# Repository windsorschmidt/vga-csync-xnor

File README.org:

* About

Combines VGA horizontal and vertical synchronization signals into 75Ω
composite sync for use with analog CRT displays such as PVMs/BVM's, or
televisions with RGBS inputs, e.g. SCART or RGB-modified televisions.

[[vga-csync-xnor.png?raw=true]]

* EDID EEPROM

An on-board EEPROM allows the adapter to store and serve an EDID to
the host PC to automatically configure a TV-compatible video mode.

In Linux, [[https://github.com/ChalkElec/write-edid][write-edid]] may be used to program the EEPROM with an
EDID. Sample EDID files have been included.

* License

Circuit schematic and PCB layout are licensed under CERN-OHL-S v2.

See [[LICENSE.txt]].

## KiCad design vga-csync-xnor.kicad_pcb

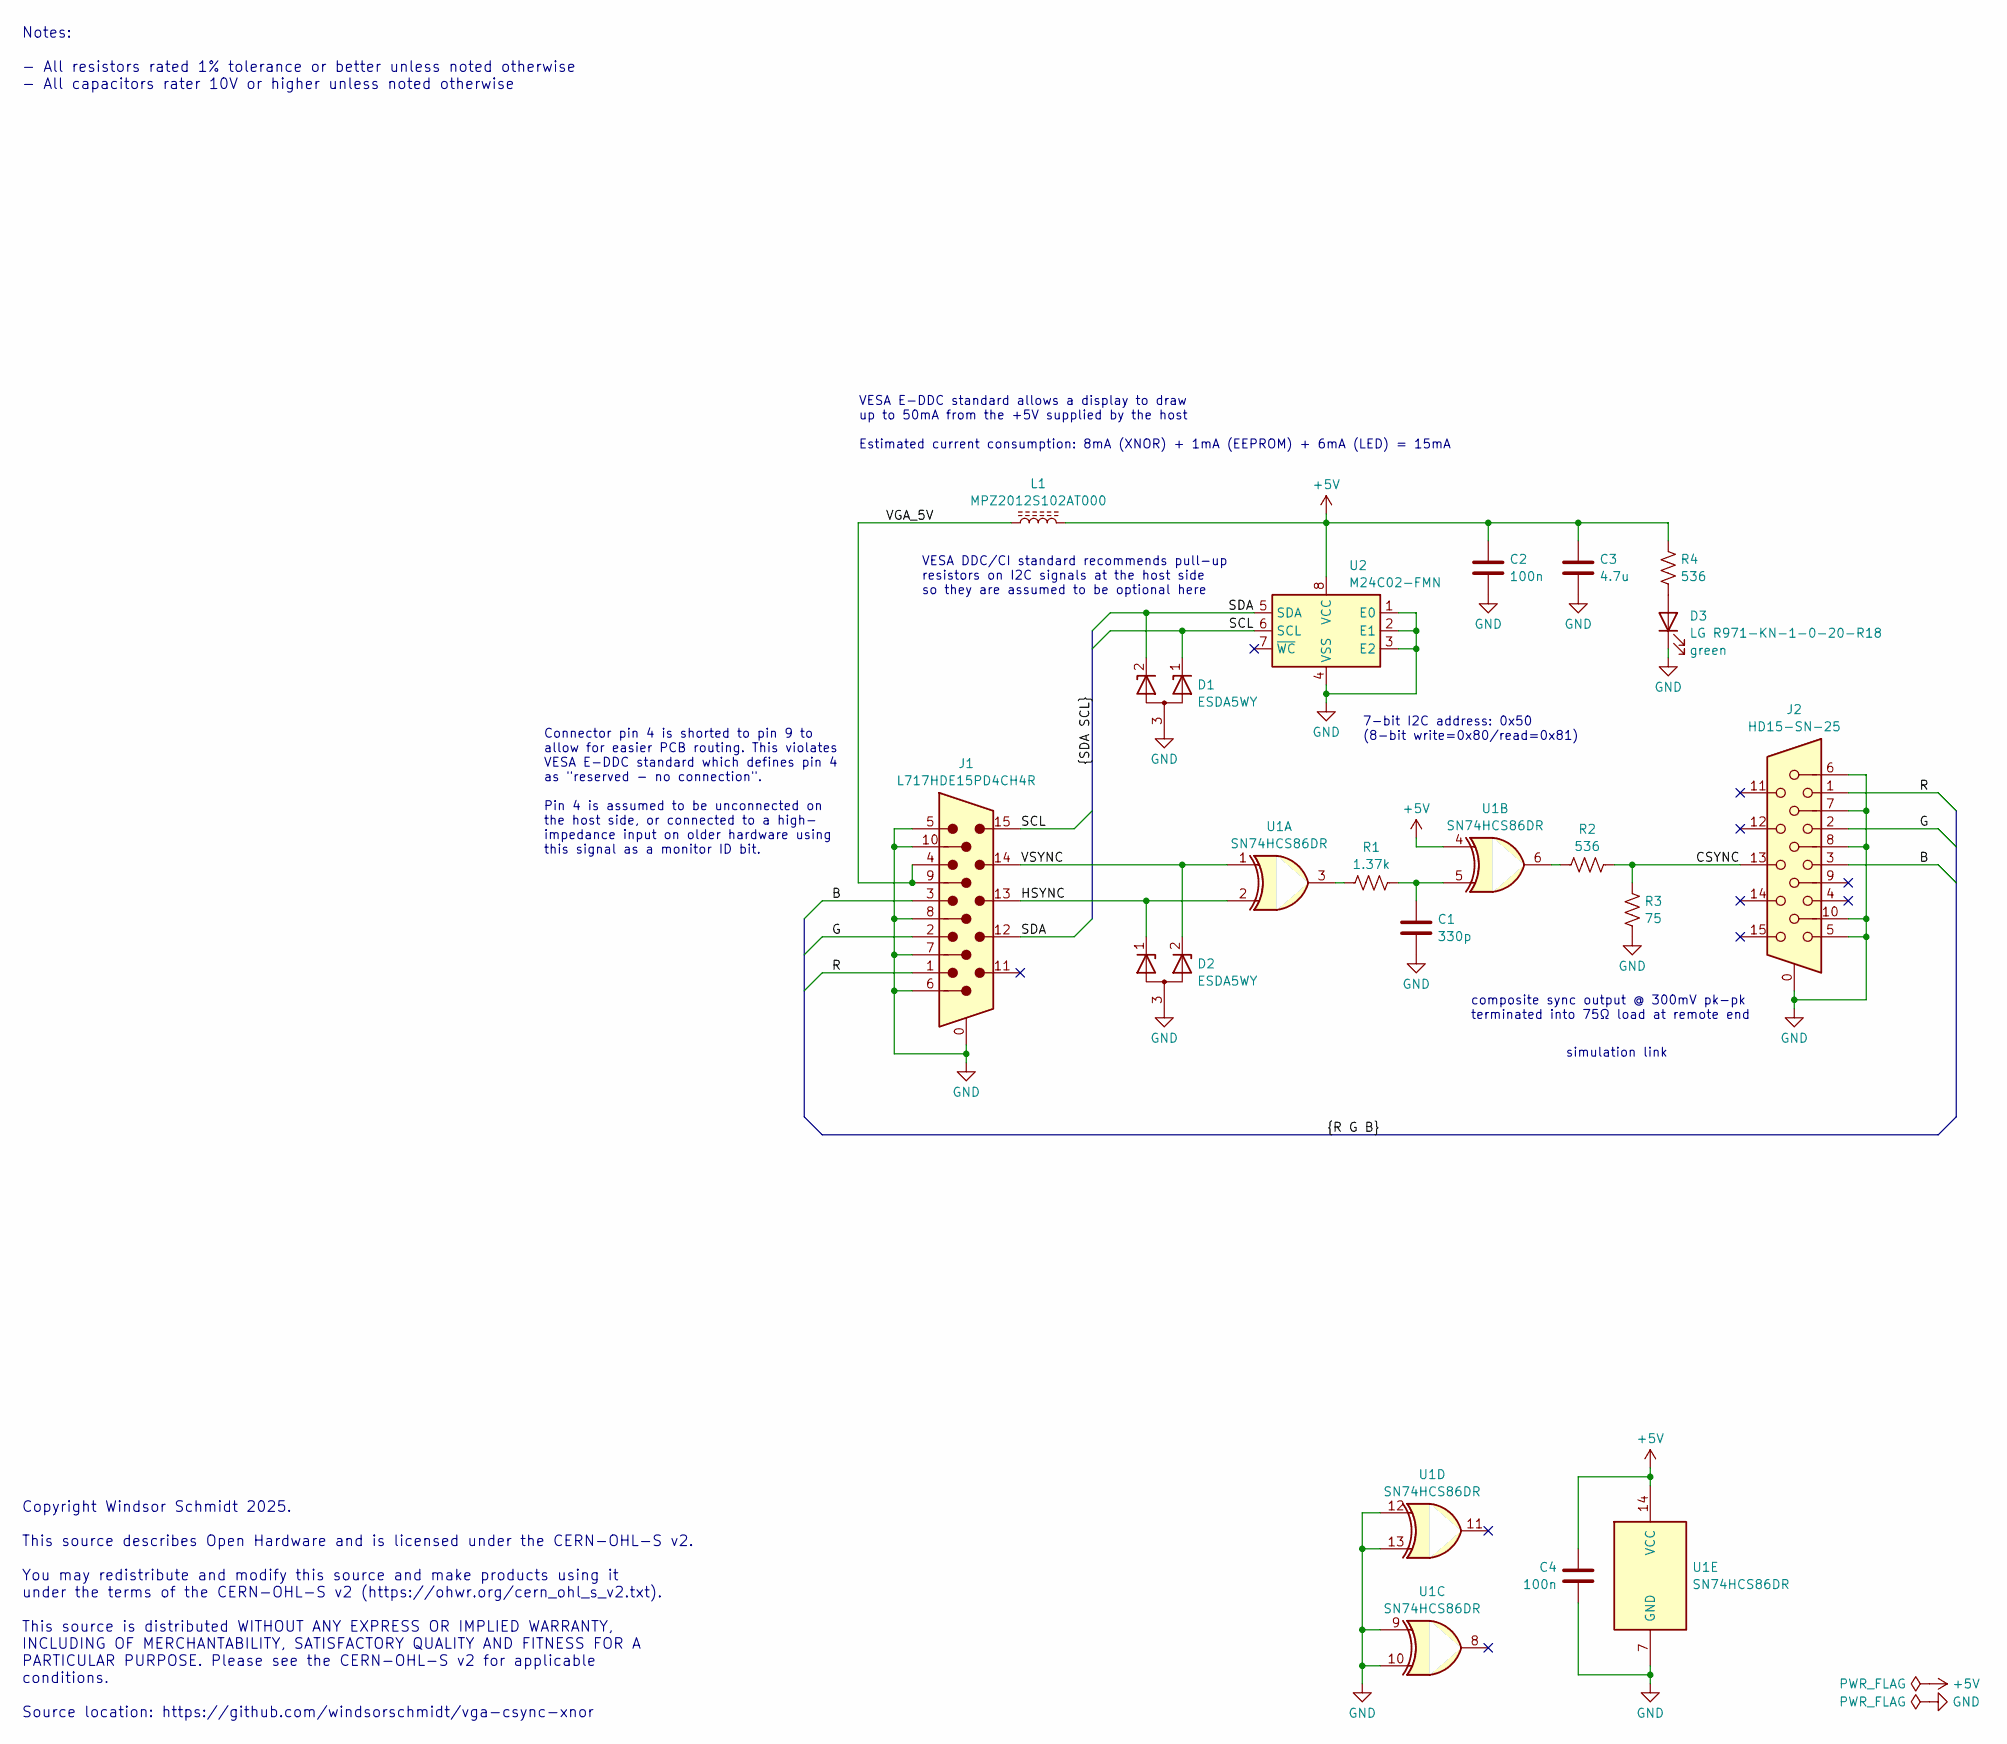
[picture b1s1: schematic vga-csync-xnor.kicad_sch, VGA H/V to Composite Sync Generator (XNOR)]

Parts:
C1: 330p; C_0603_1608Metric
C2, C4: 100n; C_0603_1608Metric
C3: 4.7u; C_0805_2012Metric
D1, D2: ESDA5WY; SOT-323_SC-70
D3: LG R971-KN-1-0-20-R18; LED_0805_2012Metric
J1: L717HDE15PD4CH4R; DSUB-15-HD_Pins_Horizontal_P2.29x1.90mm_EdgePinOffset3.03mm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
J2: HD15-SN-25; DSUB-15-HD_Socket_Horizontal_P2.29x1.90mm_EdgePinOffset3.03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
L1: MPZ2012S102AT000; L_0805_2012Metric
R1: 1.37k; R_0603_1608Metric
R2, R4: 536; R_0603_1608Metric
R3: 75; R_0603_1608Metric
U1: SN74HCS86DR; SOIC-14_3.9x8.7mm_P1.27mm
U2: M24C02-FMN; SOIC-8_3.9x4.9mm_P1.27mm

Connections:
+5V: C2.1, C3.1, C4.1, L1.2, R4.2, U1.4, U1.14 (VCC), U2.8 (VCC)
/B: J1.3, J2.3
/CSYNC: J2.13, R2.1, R3.1
/G: J1.2, J2.2
/HSYNC: D2.1 (K), J1.13, U1.2
/R: J1.1, J2.1
/SCL: D1.1 (K), J1.15, U2.6 (SCL)
/SDA: D1.2 (K), J1.12, U2.5 (SDA)
/VGA_5V: J1.4, J1.9, L1.1
/VSYNC: D2.2 (K), J1.14, U1.1
GND: C1.2, C2.2, C3.2, C4.2, D1.3 (A), D2.3 (A), D3.1 (K), J1.0, J1.5, J1.6, J1.7, J1.8, J1.10, J2.0, J2.5, J2.6, J2.7, J2.8, J2.10, R3.2, U1.7 (GND), U1.9, U1.10, U1.12, U1.13, U2.1 (E0), U2.2 (E1), U2.3 (E2), U2.4 (VSS)
unnamed: C1.1, R1.2, U1.5
unnamed: D3.2 (A), R4.1
unnamed: R1.1, U1.3
unnamed: R2.2, U1.6

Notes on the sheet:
7-bit I2C address: 0x50 (8-bit write=0x80/read=0x81)
simulation link
Notes: - All resistors rated 1% tolerance or better unless noted otherwise - All capacitors rater 10V or higher unless noted otherwise
composite sync output @ 300mV pk-pk terminated into 75Ω load at remote end
Copyright Windsor Schmidt 2025. This source describes Open Hardware and is licensed under the CERN-OHL-S v2. You may redistribute and modify this source and make products using it under the terms of the CERN-OHL-S v2 (https://ohwr.org/cern_ohl_s_v2.txt). This source is distributed WITHOUT ANY EXPRE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
VESA E-DDC standard allows a display to draw up to 50mA from the +5V supplied by the host Estimated current consumption: 8mA (XNOR) + 1mA (EEPROM) + 6mA (LED) = 15mA
VESA DDC/CI standard recommends pull-up resistors on I2C signals at the host side so they are assumed to be optional here
Connector pin 4 is shorted to pin 9 to allow for easier PCB routing. This violates VESA E-DDC standard which defines pin 4 as "reserved - no connection". Pin 4 is assumed to be unconnected on the host side, or connected to a high- impedance input on older hardware using this signal as a monitor ID 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

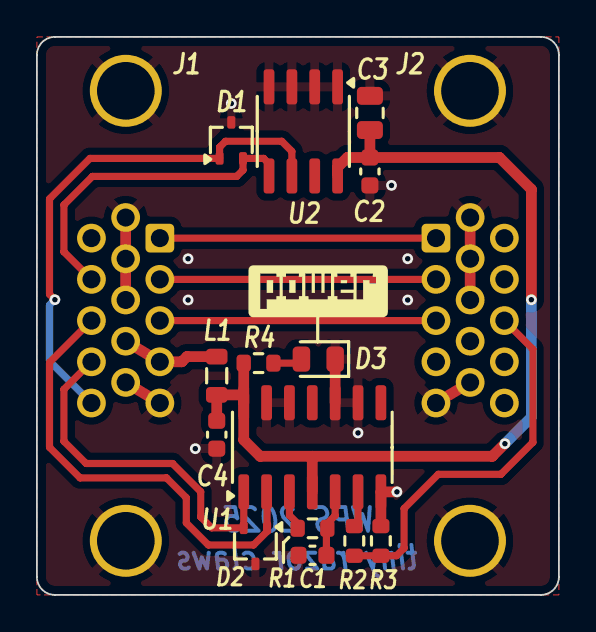
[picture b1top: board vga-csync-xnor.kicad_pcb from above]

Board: 2 copper layers, 29.0 x 31.0 mm, 16 parts (0 on the bottom side), 15 nets.

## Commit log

2025-08-04 rename file
2025-08-07 add edid files
2025-08-20 update pcb image
